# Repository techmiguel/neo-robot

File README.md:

# NEO — open-source ESP32-S3 voice assistant with an offline wake word and a local LLM

**NEO** is a DIY smart speaker built around an **ESP32-S3**. You say **"Hola NEO"**: a
15 KB **TinyML** model (TensorFlow Lite Micro, int8) recognizes the **wake word on the
chip, offline**. Then you ask anything, hands-free. A Python server on your PC transcribes
the question with **Whisper**, answers it with a **local LLM (Ollama: Gemma, Qwen)** or the
cloud (Groq), and talks back through the speaker with **streaming text-to-speech**.

It is a privacy-friendly, hackable **Alexa / Google Home alternative** you can build on a
breadboard for the price of a few modules, and **every number in this README was measured
on the real board**, with the raw data in the repo.

```mermaid
flowchart TB
    subgraph board["ESP32-S3 board"]
        direction LR
        mic["INMP441 mic"] --> ww["Wake word 'Hola NEO'<br/>TFLite Micro + ESP-NN"] --> vad["VAD<br/>300 ms pre-roll"]
        spk["DAC + amp<br/>speaker"]
    end
    subgraph server["Python server: your PC or Hugging Face Spaces"]
        direction LR
        stt["STT<br/>faster-whisper / Groq"] --> intent{"Intent"}
        intent -- command --> api["Weather, crypto,<br/>news, rates"]
        intent -- question --> llm["LLM<br/>Ollama / Groq"]
        api --> tts["TTS by fragments<br/>edge-tts / Piper"]
        llm -- tokens --> tts
    end
    vad -- "PCM 16 kHz, WebSocket" --> stt
    tts -- "PCM, streamed" --> spk
```

## Highlights

- **Offline wake word on a microcontroller.** A CNN on MFCC features, quantized to int8
  and accelerated with Espressif's ESP-NN SIMD kernels: **0.32–0.40 s per inference**,
  **~1.1 s** from the end of "Hola NEO" to NEO answering. Test accuracy 95.7 %; the full
  training pipeline is included.
- **Local-first.** The board talks to your PC on the LAN; if it is not there, it falls
  back to a cloud deployment. The server can run **fully local** (faster-whisper + Ollama)
  or on free cloud tiers (Groq + edge-tts).
- **Streaming responses.** The LLM's tokens are cut into phrases, each one is synthesized
  and sent as soon as it is ready, and the firmware starts playing after 256 ms of buffered
  audio, without waiting for the full reply.
- **Commands without an LLM.** Weather, crypto prices, tech news and Cuban informal
  exchange rates are answered by keyword intent detection and real APIs: faster, cheaper
  and no hallucinations.
- **Robust on bad networks.** Prerecorded phrases tell you when WiFi, the server or the
  internet is down. WiFi sleeps after 10 min idle and the CPU drops to 80 MHz while the
  wake word keeps listening.
- **Measured, not claimed.** Word error rate, latency per pipeline stage, wake word
  confusion matrix and power draw per state, from 31-phrase sessions read to the board.

## Quick start

You need the [hardware](#hardware), a PC on the same network (Windows, macOS or Linux) and
about 30 minutes.

### 1. Server

```bash
git clone https://github.com/techmiguel/neo-robot.git
cd neo-robot/servidor
python -m venv .venv
.venv\Scripts\activate          # Windows; on macOS/Linux: source .venv/bin/activate
pip install -e ".[dev]"
cp .env.example .env            # Windows: copy .env.example .env
```

Pick a profile and edit `.env`:

| Profile | What runs where | You need |
|---|---|---|
| `nube` (cloud, easiest) | Groq Whisper + Groq LLM + edge-tts | A free [Groq API key](https://console.groq.com/keys) in `GROQ_API_KEY` |
| `local` | faster-whisper + Ollama on your PC, edge-tts voice (Piper offline fallback) | `pip install -e ".[local]"`, [Ollama](https://ollama.com) with `ollama pull gemma4:e2b` (or `qwen2.5:3b`) |

The command APIs are optional: `OPENWEATHER_API_KEY`, `NEWSAPI_KEY` and `ELTOQUE_API_KEY`
(free tiers; CoinGecko needs no key). Every variable is explained in
[`servidor/.env.example`](servidor/.env.example).

```bash
python -m src.server.ws_server --perfil nube     # or --perfil local
```

The server listens on `ws://0.0.0.0:8765`. Note your PC's LAN IP address.

### 2. Firmware

Install [PlatformIO](https://platformio.org/install) (VS Code extension or `pip install platformio`).

```bash
cd neo-robot/firmware
cp src/config_local.example.h src/config_local.h   # Windows: copy; set NEO_SERVIDOR_HOST to your PC's IP
pio run -e esp32dev --target upload
pio device monitor -e esp32dev
```

The first build downloads the ESP32 toolchain and TensorFlow Lite Micro and takes a few
minutes. Without `config_local.h` the firmware builds with a placeholder IP (`192.168.1.100`)
and no cloud fallback.

### 3. First boot

1. NEO has no WiFi yet, so it opens an access point called **`NEO-Config`**. Join it from
   your phone and open <http://192.168.4.1>.
2. Enter your WiFi name and password. NEO saves them, connects, and finds the server.
3. Say **"Hola NEO"**, wait for the greeting and ask, in Spanish: *"¿Cuál es la capital de
   Japón?"*, *"¿Va a llover mañana en La Habana?"*, *"¿Cuánto vale el bitcoin?"*.

No wake word? Press the **BOOT** button briefly to ask without it. The model was trained on
two voices; if it does not wake for yours, [train it on your voice](#train-the-wake-word-on-your-voice).

### Troubleshooting

| Symptom | Fix |
|---|---|
| `Could not install package 'links2004/WebSockets'` on Windows | The path is too long for Windows (260 characters). Clone to a short path such as `C:\neo`. |
| `This chip is ESP8266, not ESP32-S3` while flashing | Another board is on the default port. Pass it explicitly: `--upload-port COM8` (the Freenove shows up as *USB-Enhanced-SERIAL CH343* in `pio device list`). |
| Serial log full of `ASSOC_TOOMANY` | Your access point (often a phone hotspot) has no free client slots. Disconnect a device. |
| `time: missing unit in duration "-1"` from Ollama | Use `OLLAMA_KEEP_ALIVE=-1m`, with a unit. |
| NEO hears the wake word but misses the start of your question | Wait for the greeting to finish. The VAD calibrates the background noise for 0.5 s after it. |
| The first answer takes minutes with the local profile | Ollama is loading the model from disk; later answers are fast. Keep it loaded with `OLLAMA_KEEP_ALIVE=-1m`. |

## Hardware

| Part | Notes |
|---|---|
| Freenove ESP32-S3 WROOM CAM (FNK0085), N8R8 module | 8 MB flash, 8 MB PSRAM |
| INMP441 I2S microphone | I2S_NUM_0 |
| PCM5100A + PAM8403 I2S DAC/amplifier module, 8 Ω speaker | I2S_NUM_1 |
| SSD1306 128 × 64 I2C OLED | Animated eyes and connection status |

Wiring, pin tables and the mistakes to avoid are in **[docs/hardware.md](docs/hardware.md)**.
A compact custom PCB (**NEO Lite**, 31 × 43 mm, USB-C, ready for JLCPCB assembly) is in
[`hardware/neo-lite/`](hardware/neo-lite/), designed in KiCad 9 but not yet fabricated.

## What you can ask

NEO speaks **Spanish**. After the wake word it detects the intent of the transcription:

| Intent (keywords) | Answer | Source |
|---|---|---|
| clima, "qué tiempo hace", temperatura, pronóstico | Current weather (default city: La Habana) | OpenWeatherMap |
| dólar, euro, tasa, El Toque | Informal Cuban peso (CUP) exchange rates | El Toque API |
| bitcoin, ethereum, cripto | Crypto price | CoinGecko |
| noticias, titulares | Tech news (Apple, Google, Nvidia, OpenAI…), one headline per outlet | NewsAPI |
| hola, "qué tal" | Greeting | — |
| anything else | Free answer in NEO's voice: a stranded alien traveller, curious, with dry humour, ≤ 20 words | LLM |

Adding a command is a Python class on the server (`servidor/src/commands/`); the firmware
does not change.

## Measured results

All numbers come from the board. Method, raw data and analysis are linked.

**Wake word "Hola NEO"**, CNN int8 on the ESP32-S3, two speakers
([experiments](firmware/models/experimentos/2026-10-20/RESUMEN.md), [metrics](docs/metrics/wake_word_20261020/))

| Metric | Value |
|---|---|
| Test accuracy (int8, 302 clips) | 95.7 % |
| True / false positive rate per window (threshold 0.7618) | 95.6 % / 0.6 % |
| Inference time with ESP-NN kernels | 0.32–0.40 s (2.6 s with the reference kernels) |
| End of "Hola NEO" → confirmed, on the board | **1.1 s** median (1.11 s on 24/10, n = 4; 1.09 s on 25/10, n = 5) |

**Conversation**, 31 phrases read to the board, same audio sent to every server variant.
Word error rate ignores accents. Latency runs from the end of the recording to the first
audio of the reply, median (p90).

| Session | STT + LLM + TTS | WER | Intent | Free questions | Commands |
|---|---|---|---|---|---|
| 24/10 ([analysis](docs/metrics/validacion_20261024/ANALISIS.md)) | Cloud: Groq Whisper + gpt-oss-20b + edge-tts | 3.1 % | 96.8 % | 5.7 s (8.0 s) | 5.1 s (6.1 s) |
| 24/10 | Local: Whisper small + qwen2.5:3b + edge-tts | 6.2 % | 96.8 % | 8.8 s (9.6 s) | 6.2 s (9.5 s) |
| 25/10 ([analysis](docs/metrics/validacion_gemma4_streaming/ANALISIS.md)) | Local: Whisper small + gemma4:e2b, streaming | **5.1 %** | **100 %** | 18.0 s with the long prompt* | — |

\* The 25/10 run exposed that gemma4:e2b re-processes the system prompt on every question
(~37 tokens/s on a laptop i5): the 409-token prompt cost ~8 s. The local profile now uses
a 139-token prompt (2.7–3.3 s in Ollama, not yet re-measured end to end). Streaming saves
~1.9 s once answers are long enough to split; edge-tts costs ~1.9 s per call from Cuba.
On the board, add 1.5 s of end-of-speech silence and ~0.6 s of WiFi upload.

**Power at 5 V** (INA219, [method](docs/experimento-consumo.md), [data](docs/metrics/consumo_20261024_preliminar/), preliminary)

| State | Mean current | Peak | Mean power |
|---|---|---|---|
| Rest, listening for the wake word | 119 mA | 249 mA | 0.60 W |
| Wake word capture + inference | 137 mA | 255 mA | 0.69 W |
| Sending audio over WiFi | 153 mA | 408 mA | 0.76 W |
| Speaking | 302 mA | 797 mA | 1.44 W |

## Train the wake word on your voice

The model ships in the firmware (`firmware/src/models/`) and was trained on two speakers.
The recordings are not published (they are people's voices), but the pipeline is:

```bash
cd firmware
pio run -e dataset_capture --target upload               # firmware that streams clips over serial
pip install -r tools/requirements_dataset.txt
python tools/capture_dataset.py --port COM8              # guided recording per class
pip install -r tools/requirements_train.txt
python tools/train_model.py                              # trains, quantizes to int8, exports TFLite
python tools/gen_vocabulario.py --umbrales models/umbrales.json
python tools/tflite_to_header.py                         # writes src/models/*.h
pio run -e esp32dev --target upload
```

`tools/vocabulario.json` (classes, phrases, thresholds) is the single source of truth for
capture, training and inference. The experiments behind the current model (cross-validation,
leave-one-speaker-out, negative speech) are in
[`firmware/models/experimentos/`](firmware/models/experimentos/).

## Other firmware environments

| `pio run -e …` | Purpose |
|---|---|
| `esp32dev` | Full firmware: wake word, WebSocket, audio, OLED |
| `hw_test` | Checks OLED, microphone, speaker and button |
| `loopback_test` | Plays the microphone through the speaker |
| `wake_word_test` | Wake word inference without the server |
| `dataset_capture` | Records training clips over serial |
| `demo_ojos` / `demo_bocina` | Eyes animation / speaker playback demos |
| `consumo_logger` | Power logger on an ESP8266 + INA219 |

## Benchmark your own setup

The server includes the validation panel used for every number above: it relays the board's
audio to several server variants (models, providers, streaming on/off), scores the
transcriptions against the corpus and reads the latency from the board's serial log.

```bash
cd servidor
python -m src.benchmark.panel --variante "gemma=local,OLLAMA_MODEL=gemma4:e2b" --variante "nube=nube"
```

Open <http://localhost:8080>, read the phrase it shows to NEO, and press *Generar informe*
at the end. Details in [`servidor/benchmark/README.md`](servidor/benchmark/README.md).

## Repository layout

```
firmware/            ESP32-S3 firmware (C++, PlatformIO + Arduino)
  src/               audio, display, network, commands (TFLite inference), main.cpp
  tools/             dataset capture, training, header generation, log analysis
  models/            trained models and the experiments behind them
  logs/              serial logs of the measured sessions
servidor/            Python server: STT, intent, LLM, TTS, WebSocket, benchmark panel
hardware/neo-lite/   custom PCB: KiCad project, generator scripts, Gerbers, BOM
docs/                design notes, experiments and measured metrics (in Spanish)
ROADMAP.md           phases and status (in Spanish)
```

## Documentation

The design notes and experiment reports are written in Spanish.

| Topic | Document |
|---|---|
| Wiring and parts | [docs/hardware.md](docs/hardware.md) |
| Software strategy: voice, prerecorded phrases, network on demand | [docs/estrategia-software.md](docs/estrategia-software.md) |
| Streaming responses and where the latency goes | [docs/streaming-latencia.md](docs/streaming-latencia.md) |
| Conversation memory | [docs/diseno-memoria.md](docs/diseno-memoria.md) |
| Experiments: latency, wake word latency, false positives, full flow, power | [`docs/experimento-*.md`](docs/) |
| Measured sessions | [docs/metrics/](docs/metrics/) |
| Custom PCB, phase by phase | [hardware/neo-lite/README.md](hardware/neo-lite/README.md) |
| Status and next steps | [ROADMAP.md](ROADMAP.md) |

## Design decisions

- **Only the wake word runs on the chip.** A multi-command local classifier would need a
  dataset per phrase and a reflash per change. Commands live on the server and grow without
  touching the firmware; the cost is that every question needs the network.
- **Keywords before the LLM.** Common commands skip the LLM: faster, free and
  deterministic. The LLM only gets free-form questions.
- **Two I2S buses.** Microphone and DAC each get their own peripheral; no time multiplexing.
- **Inference buffers in internal SRAM.** PSRAM access with WiFi active tripped the watchdog.
- **One voice.** NEO always speaks with edge-tts `es-CU-ManuelNeural`, including its
  prerecorded phrases; Piper only answers when edge-tts is unreachable.

## Failure modes

Every message below is prerecorded in the firmware, so NEO can say it without a server.

| Situation | What NEO does |
|---|---|
| Server unreachable (LAN and cloud) | Says "No encuentro mi servidor", and "Ya estoy conectado y listo" when it is back |
| WiFi down | Says it cannot connect; the wake word keeps working |
| No internet on the server | The server sends `sin_internet`; NEO says "No puedo acceder a internet ahora" |
| Empty transcription | "No te entendí, ¿me lo repites?" and listens again |
| Server silent for 30 s | "Está tardando demasiado, inténtalo otra vez" |
| edge-tts unreachable | The server answers with Piper (different voice) |
| LLM drifts into another script (qwen2.5:3b → Chinese) | The server asks again once, then strips non-Latin text |
| Wake word false positive | NEO greets, hears nothing for 10 s and goes back to rest |

## Security and limitations

- The WebSocket has **no authentication**; it assumes a trusted LAN. Add a token or TLS
  before exposing the server. API keys live in `servidor/.env` (gitignored).
- **Spanish only**: STT, prompts and voice.
- **Short memory**: the last 5 exchanges per WebSocket session, in RAM.
- **USB power**: speaking peaks at ~0.8 A at 5 V; a single boosted 18650 cell browns out.
- **No OTA updates** yet; flash over USB.
- The local profile is slower and less accurate than the cloud one on a laptop CPU.

## Contributing

Issues and pull requests are welcome; see [CONTRIBUTING.md](CONTRIBUTING.md). Run the tests
before sending changes:

```bash
cd servidor && pytest
cd firmware/tools && pytest
```

## License and acknowledgements

[MIT](LICENSE). Built on [TensorFlow Lite Micro](https://github.com/espressif/esp-tflite-micro),
[ESP-NN](https://github.com/espressif/esp-nn), [faster-whisper](https://github.com/SYSTRAN/faster-whisper),
[Ollama](https://ollama.com), [Groq](https://groq.com), [edge-tts](https://github.com/rany2/edge-tts),
[Piper](https://github.com/rhasspy/piper), [Adafruit SSD1306](https://github.com/adafruit/Adafruit_SSD1306)
and [arduinoWebSockets](https://github.com/Links2004/arduinoWebSockets).

*¿Hablas español?* Lee el [README en español](README.es.md).

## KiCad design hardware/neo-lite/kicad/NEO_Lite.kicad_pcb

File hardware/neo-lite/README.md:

# NEO Lite — hardware

Placa económica y compacta (31 × 43 mm, 2 capas, revisión C) para NEO: módulo ESP32-S3-WROOM-1-N16R8 con su
antena integrada sobresaliendo del borde, USB-C con el USB nativo del S3 (sin puente USB-UART), conector para el
micrófono INMP441, amplificador I2S MAX98357A con salida de dos pines para el altavoz y conector
I2C para la OLED SSD1306. Montaje SMT de JLCPCB por una cara; conectores soldados a mano.

Es un diseño propio, independiente de NEO v2 (`hardware/neo-v2`, derivado de Home Assistant Voice
PE), que se descartó por coste. Mantiene el chip, la memoria y los pines de audio con los que ya
funciona el firmware, así que el modelo de wake word no cambia.

## Estado

| Fase | Contenido | Estado |
|---|---|---|
| 1 | Selección de componentes, BOM y coste | Entregada: `docs/fase1-componentes.md` |
| 2 | Esquemático (KiCad 9) y ERC | Entregada: `docs/fase2-esquematico.md`, `docs/esquematico_neo_lite.pdf`; ERC 0/0 |
| 3 | Colocación y PCB | Entregada (revisión B): `docs/fase3-colocacion.md`; 31 × 43 mm, DRC sin errores (sin rutear) |
| 4 | Ruteo y DRC | Entregada: `docs/fase4-ruteo.md`; DRC sin errores ni conexiones pendientes, paridad con el esquemático |
| 5 | Fabricación (Gerber, BOM, CPL) | Entregada: `docs/fase5-fabricacion.md`; paquete en `production/` |
| 6 | Revisión del PCB antes de fabricar: enchufado en caliente, USB-C, par USB, desacoplo, disipación de U1 | Entregada (revisión C): `docs/fase6-revision.md`; `tools/review_pcb.py` sin fallos |
| 7 | Firmware: entorno de la placa (USB CDC, pines de la OLED, SD_MODE) | Pendiente |

## Herramientas

`tools/gen_schematic.py` genera el esquemático (`kicad/NEO_Lite.kicad_sch`) y
`tools/verify_schematic.py` lo comprueba contra su descripción, las reglas eléctricas y la BOM;
requieren KiCad 9 y `sexpdata` (uso en `docs/fase2-esquematico.md`). `tools/build_pcb.py` crea el PCB
desde la netlist con la colocación de la fase 3 y `tools/plot_placement.py` dibuja la vista de
colocación con ratsnest (`docs/fase3-colocacion.md`). `tools/preroute.py` traza las pistas fijas (par USB,
+3V3 y EN de la columna izquierda, lengüeta de U1). `tools/route_all.py` rutea el resto con Freerouting
(`route_pcb.py`), añade los planos y comprueba el DRC y las reglas de ruteo de `tools/review_pcb.py`
(`docs/fase4-ruteo.md`, `docs/fase6-revision.md`). `tools/hotplug_sim.py` simula el pico de tensión al
enchufar el USB. `tools/silk_cleanup.py`
limpia y rotula la serigrafía y `tools/fab_outputs.py` genera `production/` (Gerber, taladros, BOM y
CPL de JLCPCB) y la tabla de rotaciones (`docs/fase5-fabricacion.md`).

`tools/jlc_search.py` consulta el buscador de piezas de JLCPCB y guarda una instantánea en
`docs/data/jlc_cache.json`. `tools/bom_fase1.py` genera `docs/data/bom_fase1.csv` y el desglose
de coste del pedido; solo requieren Python 3.

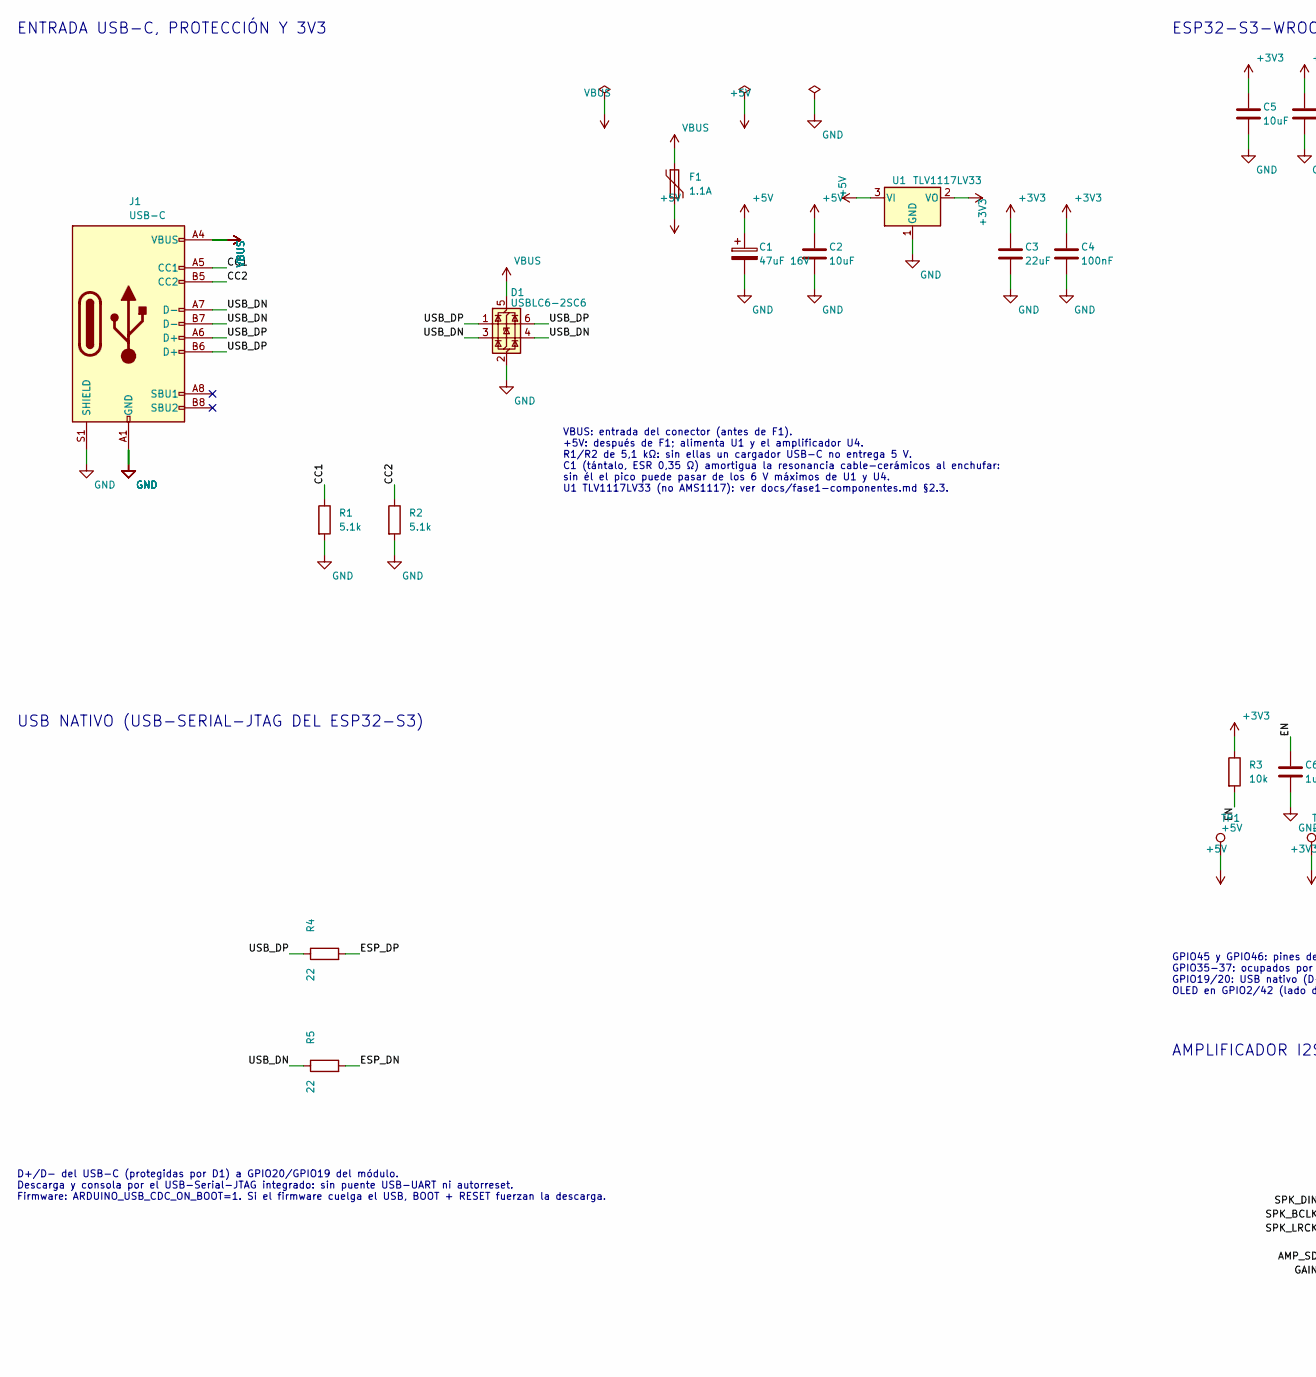
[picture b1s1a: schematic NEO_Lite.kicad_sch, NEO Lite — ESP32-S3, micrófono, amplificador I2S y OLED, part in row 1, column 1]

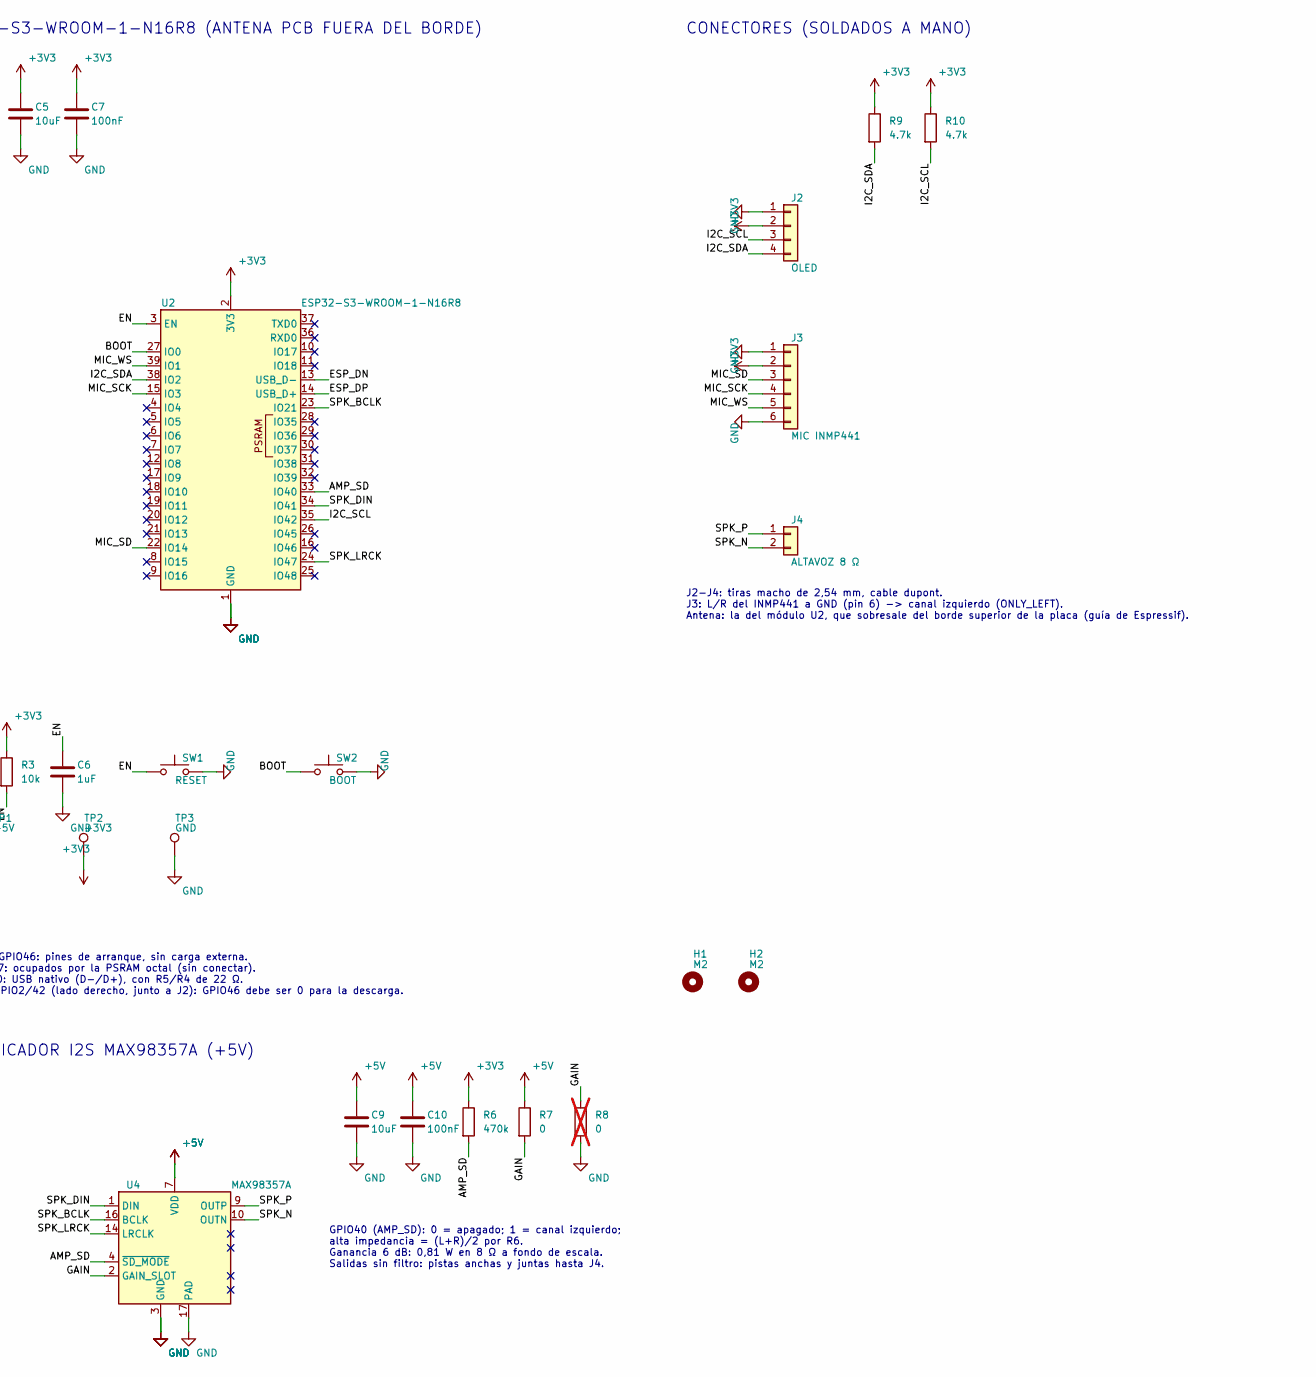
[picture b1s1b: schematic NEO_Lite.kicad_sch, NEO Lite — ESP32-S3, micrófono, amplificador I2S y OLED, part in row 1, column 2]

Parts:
C1: 47uF 16V; CP_EIA-6032-28_Kemet-C; MPN TPSC476K016R0350; LCSC C444805
C2, C5, C9: 10uF; C_0805_2012Metric; LCSC C15850
C3: 22uF; C_0805_2012Metric; LCSC C45783
C4, C7, C10: 100nF; C_0402_1005Metric; LCSC C1525
C6: 1uF; C_0402_1005Metric; LCSC C52923
D1: USBLC6-2SC6; SOT-23-6; MPN USBLC6-2SC6; LCSC C7519
F1: 1.1A; Fuse_1206_3216Metric; MPN BSMD1206-110-6V; LCSC C2803344
H1, H2: M2; MountingHole_2.2mm_M2
J1: USB-C; USB_C_Receptacle_HRO_TYPE-C-31-M-12; MPN TYPE-C-31-M-12; LCSC C165948
J2: OLED; PinHeader_1x04_P2.54mm_Vertical
J3: MIC INMP441; PinHeader_1x06_P2.54mm_Vertical
J4: ALTAVOZ 8 Ω; PinHeader_1x02_P2.54mm_Vertical
R1, R2: 5.1k; R_0402_1005Metric; LCSC C25905
R3: 10k; R_0402_1005Metric; LCSC C25744
R4, R5: 22; R_0402_1005Metric; LCSC C25092
R6: 470k; R_0402_1005Metric; LCSC C25790
R7: 0; R_0402_1005Metric; LCSC C17168
R8: 0; R_0402_1005Metric; LCSC C17168; not fitted
R9, R10: 4.7k; R_0402_1005Metric; LCSC C25900
SW1: RESET; SW_Push_1P1T_XKB_TS-1187A; LCSC C318884
SW2: BOOT; SW_Push_1P1T_XKB_TS-1187A; LCSC C318884
TP1: +5V; TestPoint_Pad_D1.0mm
TP2: +3V3; TestPoint_Pad_D1.0mm
TP3: GND; TestPoint_Pad_D1.0mm
U1: TLV1117LV33; SOT-223-3_TabPin2; MPN TLV1117LV33DCYR; LCSC C15578
U2: ESP32-S3-WROOM-1-N16R8; ESP32-S3-WROOM-1; MPN ESP32-S3-WROOM-1-N16R8; LCSC C2913202
U4: MAX98357A; TQFN-16-1EP_3x3mm_P0.5mm_EP1.23x1.23mm; MPN MAX98357AETE+T; LCSC C910544

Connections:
+3V3: C3.1, C4.1, C5.1, C7.1, J2.2, J3.2, R3.1, R6.1, R9.1, R10.1, TP2.1, U1.2 (VO), U2.2 (3V3)
+5V: C1.1, C2.1, C9.1, C10.1, F1.2, R7.1, TP1.1, U1.3 (VI), U4.7 (VDD), U4.8 (VDD)
/AMP_SD: R6.2, U2.33 (IO40), U4.4 (~SD_MODE)
/BOOT: SW2.1, U2.27 (IO0)
/CC1: J1.A5 (CC1), R1.1
/CC2: J1.B5 (CC2), R2.1
/EN: C6.1, R3.2, SW1.1, U2.3 (EN)
/ESP_DN: R5.2, U2.13 (USB_D-)
/ESP_DP: R4.2, U2.14 (USB_D+)
/GAIN: R7.2, R8.1, U4.2 (GAIN_SLOT)
/I2C_SCL: J2.3, R10.2, U2.35 (IO42)
/I2C_SDA: J2.4, R9.2, U2.38 (IO2)
/MIC_SCK: J3.4, U2.15 (IO3)
/MIC_SD: J3.3, U2.22 (IO14)
/MIC_WS: J3.5, U2.39 (IO1)
/SPK_BCLK: U2.23 (IO21), U4.16 (BCLK)
/SPK_DIN: U2.34 (IO41), U4.1 (DIN)
/SPK_LRCK: U2.24 (IO47), U4.14 (LRCLK)
/SPK_N: J4.2, U4.10 (OUTN)
/SPK_P: J4.1, U4.9 (OUTP)
/USB_DN: D1.3 (I/O2), D1.4 (I/O2), J1.A7 (D-), J1.B7 (D-), R5.1
/USB_DP: D1.1 (I/O1), D1.6 (I/O1), J1.A6 (D+), J1.B6 (D+), R4.1
GND: C1.2, C2.2, C3.2, C4.2, C5.2, C6.2, C7.2, C9.2, C10.2, D1.2 (GND), J1.A1 (GND), J1.A12 (GND), J1.B1 (GND), J1.B12 (GND), J1.S1 (SHIELD), J2.1, J3.1, J3.6, R1.2, R2.2, R8.2, SW1.2, SW2.2, TP3.1, U1.1 (GND), U2.1 (GND), U2.40 (GND), U2.41 (GND), U4.3 (GND), U4.11 (GND), U4.15 (GND), U4.17 (PAD)
VBUS: D1.5 (VBUS), F1.1, J1.A4 (VBUS), J1.A9 (VBUS), J1.B4 (VBUS), J1.B9 (VBUS)

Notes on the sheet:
ENTRADA USB-C, PROTECCIÓN Y 3V3
VBUS: entrada del conector (antes de F1). +5V: después de F1; alimenta U1 y el amplificador U4. R1/R2 de 5,1 kΩ: sin ellas un cargador USB-C no entrega 5 V. C1 (tántalo, ESR 0,35 Ω) amortigua la resonancia cable-cerámicos al enchufar: sin él el pico puede pasar de los 6 V máximos de U1 y U4. U1 TLV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
USB NATIVO (USB-SERIAL-JTAG DEL ESP32-S3)
D+/D- del USB-C (protegidas por D1) a GPIO20/GPIO19 del módulo. Descarga y consola por el USB-Serial-JTAG integrado: sin puente USB-UART ni autorreset. Firmware: ARDUINO_USB_CDC_ON_BOOT=1. Si el firmware cuelga el USB, BOOT + RESET fuerzan la descarga.
ESP32-S3-WROOM-1-N16R8 (ANTENA PCB FUERA DEL BORDE)
GPIO45 y GPIO46: pines de arranque, sin carga externa. GPIO35-37: ocupados por la PSRAM octal (sin conectar). GPIO19/20: USB nativo (D-/D+), con R5/R4 de 22 Ω. OLED en GPIO2/42 (lado derecho, junto a J2): GPIO46 debe ser 0 para la descarga.
AMPLIFICADOR I2S MAX98357A (+5V)
GPIO40 (AMP_SD): 0 = apagado; 1 = canal izquierdo; alta impedancia = (L+R)/2 por R6. Ganancia 6 dB: 0,81 W en 8 Ω a fondo de escala. Salidas sin filtro: pistas anchas y juntas hasta J4.
CONECTORES (SOLDADOS A MANO)
J2-J4: tiras macho de 2,54 mm, cable dupont. J3: L/R del INMP441 a GND (pin 6) -> canal izquierdo (ONLY_LEFT). Antena: la del módulo U2, que sobresale del borde superior de la placa (guía de Espressif).

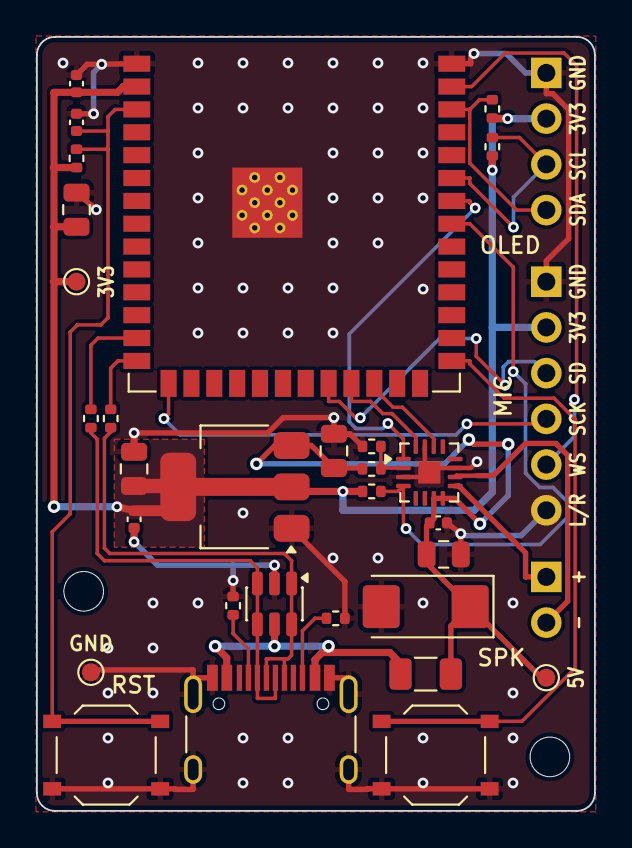
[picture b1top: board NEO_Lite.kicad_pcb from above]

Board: 2 copper layers, 31.0 x 43.0 mm, 35 parts (0 on the bottom side), 24 nets.

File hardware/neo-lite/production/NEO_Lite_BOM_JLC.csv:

Comment,Designator,Footprint,LCSC Part #
47uF 16V,C1,CP_EIA-6032-28_Kemet-C,C444805
10uF,"C2,C5,C9",C_0805_2012Metric,C15850
22uF,C3,C_0805_2012Metric,C45783
100nF,"C4,C7,C10",C_0402_1005Metric,C1525
1uF,C6,C_0402_1005Metric,C52923
USBLC6-2SC6,D1,SOT-23-6,C7519
1.1A,F1,Fuse_1206_3216Metric,C2803344
USB-C,J1,USB_C_Receptacle_HRO_TYPE-C-31-M-12,C165948
5.1k,"R1,R2",R_0402_1005Metric,C25905
10k,R3,R_0402_1005Metric,C25744
22,"R4,R5",R_0402_1005Metric,C25092
470k,R6,R_0402_1005Metric,C25790
0,R7,R_0402_1005Metric,C17168
4.7k,"R9,R10",R_0402_1005Metric,C25900
RESET,SW1,SW_Push_1P1T_XKB_TS-1187A,C318884
BOOT,SW2,SW_Push_1P1T_XKB_TS-1187A,C318884
TLV1117LV33,U1,SOT-223-3_TabPin2,C15578
ESP32-S3-WROOM-1-N16R8,U2,ESP32-S3-WROOM-1,C2913202
MAX98357A,U4,TQFN-16-1EP_3x3mm_P0.5mm_EP1.23x1.23mm,C910544

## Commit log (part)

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2026-04-22 chore: initialize NEO robot project
    - Add ROADMAP with 8-phase development plan
    - Add ESP32-S3 firmware skeleton (PlatformIO + Arduino framework)
    - Configure board: Le-ESP32-S3-Lipo (ESP32-S3-WROOM)
    - Add module stubs: audio, display, network, commands
    - Add Unity test framework placeholder
    - Add .gitattributes for cross-platform line endings
2026-04-22 feat(oled): implement SSD1306 display driver (module 1.1)
    - Add Oled class with U8g2 full-buffer mode
    - Support single line, two lines, and status display
    - Wire to I2C pins IO8/IO9 (Le-ESP32-S3-Lipo)
    - Update main.cpp to test display on boot with LED feedback
2026-04-22 fix(oled): switch from U8g2 to Adafruit SSD1306 for ESP32-S3 compatibility
    U8g2 triggers a watchdog crash on ESP32-S3 Arduino core 3.x because its
    non-trivial constructor runs in global scope before the CPU clock is
    initialized. The Adafruit SSD1306 + GFX stack combined with a static-local
    instance inside setup() avoids the static init order issue.
    - Replace U8g2 deps with Adafruit SSD1306 ^2.5.13 and GFX ^1.11.11
    - Rewrite oled wrapper against Adafruit_SSD1306 API
2026-04-23 feat(display): add animated robot eyes on OLED (module 1.1+)
    Implement a non-blocking eye animation state machine using millis()
    instead of delay(). Eyes cycle through blink, look left/right, and
    happy expressions with random 2-4s intervals between animations.
    - Add Face class (face.h / face.cpp) with AnimState enum
    - Add Oled::rawDisplay() accessor for display object sharing
    - Simplify loop() to a single face->update(millis()) call
2026-04-23 feat(audio): implement INMP441 microphone driver via I2S (module 1.2)
    Read 16-bit PCM audio at 16 kHz from INMP441 using I2S_NUM_0.
    Includes RMS level calculation and serial/OLED/LED test output.
    - Configure I2S with 32-bit frames, left channel only (L/R tied to GND)
    - Convert raw int32 to int16 by taking the 16 MSBs of each frame
    - Add Microphone::rms() for amplitude monitoring
2026-04-23 feat(audio): implement PCM5100A+PAM8403 speaker driver via I2S (module 1.3)
    Output 16-bit PCM audio at 16 kHz using I2S_NUM_1 with 32-bit frames.
    PCM5100A (24-bit DAC) requires 32-bit I2S frames to lock its internal PLL.
    SCK pin must be tied to GND to enable PLL mode — without this the DAC
    accepts I2S data but produces no analog output.
    - Configure I2S_NUM_1 as TX master, 32-bit stereo frames
    - Expand int16 mono samples to int32 MSB-aligned before writing
2026-04-23 feat(wifi): add WiFi manager with NVS storage and AP config portal
    Implements module 1.4: WifiManager class stores credentials in NVS and
    connects automatically on boot. If no credentials exist or connection
    fails, opens AP "NEO-Config" with HTTP portal at 192.168.4.1 for
    one-time setup. Portal redirects unknown URLs for captive portal UX.
    Also: remove LED/NeoPixel calls from all files (no LED hardware),
    upgrade audio sample rate to 24 kHz, fix src_filter deprecation
2026-04-23 feat(servidor): add STT/LLM/TTS pipeline with Groq cloud backend
    Implements modules 2.1-2.5: Transcriber (Groq Whisper), LLMClient
    (Groq Llama 3.1), Synthesizer (edge-tts 24 kHz). Pipeline verified
    end-to-end: STT 1.9s + LLM 0.84s + TTS 1.6s = 4.36s total latency.
    Both backends (groq/ollama, groq/local) selectable via .env.
2026-04-23 feat(servidor): add WebSocket server with echo/pipeline modes and echo tests
    Implements module 2.4: asyncio WebSocket server on port 8765 with
    switchable modes (WS_MODO=echo|pipeline). Echo mode verified stable
    over 10 consecutive rounds without frame loss (pytest green).
2026-04-23 feat(ws): implement WebSocket client on ESP32 and fix server deprecation warning
    Module 3.1: WsClient class wraps ArduinoWebsockets with text/binary
    callbacks and poll-based event loop. Connection to Python server verified
    stable with 10-minute ping test (10s interval, zero disconnections).
    Also removes deprecated WebSocketServerProtocol type hints from ws_server.
2026-04-26 feat(firmware): implement record-then-send audio pipeline with BOOT trigger
    - Add Trigger class (GPIO0/BOOT) with debounce, designed to be swapped
    later by TFLite wake-word without changing the rest of the system
    - Rework main.cpp into two strict phases: pure I2S recording (no WiFi
    calls), then WebSocket send — prevents DMA corruption from WiFi ISR
    - Pre-allocate 96 KB static buffer for 3 s of 16 kHz PCM; no heap
2026-04-26 fix(servidor): save debug WAV and correct STT sample rate to 16 kHz
    - Save received PCM as grabacion_esp32.wav in both echo and pipeline modes
    - Fix STT sample rate: was incorrectly set to 24000 Hz (TTS output rate)
    instead of 16000 Hz (INMP441 capture rate), causing wrong transcriptions
2026-04-26 feat(firmware): complete bidirectional audio pipeline (module 3.3)
    - Receive TTS response as binary PCM chunks via WebSocket and accumulate
    in the existing 96 KB audio buffer (reused after recording phase)
    - Play back response through Speaker once fin_respuesta is received
    - Align sample rates: speaker and TTS synthesizer both set to 16 kHz,
    eliminating the 24/16 kHz mismatch; enable APLL on speaker I2S
2026-04-26 feat(firmware): add VAD and PSRAM audio buffer (module 3.4)
    - Replace fixed 3s recording with energy-based VAD:
    calibrates noise floor on trigger, waits for voice onset (6x floor),
    records until 1.5s of sustained silence or 30s max
    - Smooth RMS with IIR (0.7/0.3) before silence comparison to prevent
    single noisy blocks from resetting the hold timer
    - Allocate audio buffer from PSRAM (30s / 960 KB) with fallback to
2026-04-26 fix(servidor): async TTS, load .env in server, tighten LLM responses
    - Make synthesize() async to avoid nested asyncio.run() inside WS handler
    - Add load_dotenv() to ws_server so WS_MODO=pipeline is read from .env
    - Constrain LLM to one direct sentence (max 60 tokens) to keep TTS audio
    within playback buffer limits
    - Add miniaudio to pyproject.toml dependencies
2026-04-28 feat(deploy): add HF Spaces Docker config, WSS client, Phase 5 handlers
2026-04-28 feat(deploy): add HF Spaces Docker config, WSS client, Phase 5 handlers
2026-04-28 fix(servidor): update process_request signature for websockets 12.x
    The old (path, headers) signature silently fails in websockets >=12
    (asyncio API), causing _health() to never intercept GET requests and
    the server to return 426 to all plain HTTP clients.
    Switch to (connection, request) with connection.respond(), which is
    the correct API for websockets >=12.0 asyncio server.
    Also document ELTOQUE_API_KEY in .env.example.
2026-04-28 feat(firmware): connect to HF Spaces via WSS with auto-retry
    - Remove HTTP wake-up GET before WS connect: the HTTPClient SSL context
    leaked socket fd 0 into the next SSL attempt, causing start_ssl_client
    to fail with errno EBADF on the WsClient connection.
    - Replace single connect-or-halt with a retry loop (5 s interval) so
    the ESP32 waits for the HF Space to wake up on first boot.
    - Fix loop() reconnect to use conectarSeguro() in cloud mode instead
2026-04-29 feat(firmware+servidor): fix WS dropout over mobile by moving I/O to FreeRTOS Core 0
    Firmware:
    - Add tareaWs FreeRTOS task pinned to Core 0 (same core as WiFi stack).
    Audio chunks are sent with vTaskDelay(10ms) between each, yielding CPU
    to the TCP/IP layer to process ACKs without contention from the main loop.
    - Main loop (Core 1) blocks on ulTaskNotifyTake() during send phase.
    This eliminates the CPU starvation that caused TCP buffer overflow and
2026-04-29 ci: add workflow_dispatch trigger to HF deploy
2026-04-29 fix(ci): use correct secret name NEOTOKENHF for HF deploy
2026-04-29 fix(ws): resolve WebSocket upgrade blocked by health check and add resilience
    - ws_server: _health now skips response when Upgrade: websocket header is present.
    In websockets >=12.x, process_request intercepts WS upgrades and returning a
    response sends 200 instead of 101, causing the ESP32 to enter a disconnect loop.
    - firmware: change WS path from '/' to '/ws' so health check never matches WS requests.
    - ws_client: increase TLS timeout to 15s, add heap diagnostics on connect/disconnect.
    - main: FreeRTOS ws_task stack 16 KB, WiFi restart every 4 failed attempts,
2026-04-29 fix(server): remove undefined _guardar_wav call that crashed handler on fin_grabacion
    _modo_echo called _guardar_wav which was never defined, raising NameError.
    The exception propagated out of the handler coroutine, causing websockets to
    close the connection silently — the ESP32 saw an immediate disconnect after
    fin_grabacion with no server response.
    - Remove _guardar_wav call from _modo_echo (echo mode sends audio back directly)
    - Default WS_MODO to pipeline instead of echo (production deployment)
2026-04-30 feat(server): add direct hola command handler
    Add a dedicated hola handler and register it in the command router so HOLA_NEO can return a fixed TTS greeting from HF without falling back to unknown-command responses.
    Made-with: Cursor
2026-05-03 fix(server): set default city to La Habana and reduce keepalive to 2s
    - Default city in clima handler changed to La Habana
    - WebSocket keepalive interval reduced from 5s to 2s for better
    resilience against mobile carrier proxy timeouts
2026-05-03 feat(firmware): complete dispatcher routing and remove dev test pins
    - Implement full command dispatch for 13 commands (CLIMA, NOTICIAS,
    ELTOQUE, CRIPTO, DADO, HOLA_NEO as direct; TEMPORIZADOR, BUSCAR,
    TRADUCIR, RECORDATORIO, CALCULAR, TRIVIA as hybrid grab-and-send)
    - Remove 10 individual test GPIO pins (PINES_CMD) used during development
    - Remove 4x4 keyboard driver files (keyboard.h/cpp), also dev-only
    - Remove idle light sleep logic (replaced by always-on mic in phase 4)
2026-05-03 feat(firmware): add dataset capture firmware and PC collection script
    - New PlatformIO env [dataset_capture]: records 1s audio samples and
    sends them to PC via Serial (460800 baud, raw PCM 16-bit 16kHz mono)
    - BOOT button: short press records current class, long press cycles class
    - Serial protocol: RECORD:{class} → RECORDING / START_AUDIO:N / [PCM] / END_AUDIO
    - tools/capture_dataset.py: interactive PC script; keys 1/2/3 trigger
    recording for hola_neo / desconocido / silencio; saves as WAV files
2026-05-03 fix(dataset): use 115200 baud and tolerate unexpected serial lines
    - Firmware: lower baud to 115200 (matches project standard, avoids CH340C issues)
    - Python: open serial with dsrdtr=False/rtscts=False to prevent accidental
    ESP32 resets during the capture session
    - Python: replace strict leer_linea() checks with esperar_linea() that
    silently skips ROM boot messages and debug lines until the expected
    prefix is found
2026-05-03 feat(tools): add TensorFlow training script for wake word model
    - Extracts MFCC features with tensorflow.signal (same params to replicate in C++)
    - Data augmentation x7: gaussian noise (20/12 dB SNR), time shift ±150ms, volume ±20%
    - CNN architecture: 3x [Conv2D+BN+ReLU+MaxPool] + GAP + Dense (~28K params)
    - Early stopping + ReduceLROnPlateau callbacks
    - Exports models/modelo_float.tflite and models/modelo_int8.tflite
    - Prints confusion matrix and classification report
2026-05-03 feat(firmware): implement TFLite Micro wake word inference pipeline
    Add always-on wake word detection for "Hola NEO" using a trained
    CNN int8 model (39 KB) embedded in firmware flash.
    - Add MFCC extractor (audio/mfcc.h/cpp): 512-pt FFT, Mel filterbank,
    DCT-II; exact match with train_model.py parameters
    - Add mel_filterbank.h (generated): 48 KB const arrays in .rodata
    (g_mel_w[257][40], g_hann_win[400], g_dct_m[40][40])

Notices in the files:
README.md:
License: MIT
